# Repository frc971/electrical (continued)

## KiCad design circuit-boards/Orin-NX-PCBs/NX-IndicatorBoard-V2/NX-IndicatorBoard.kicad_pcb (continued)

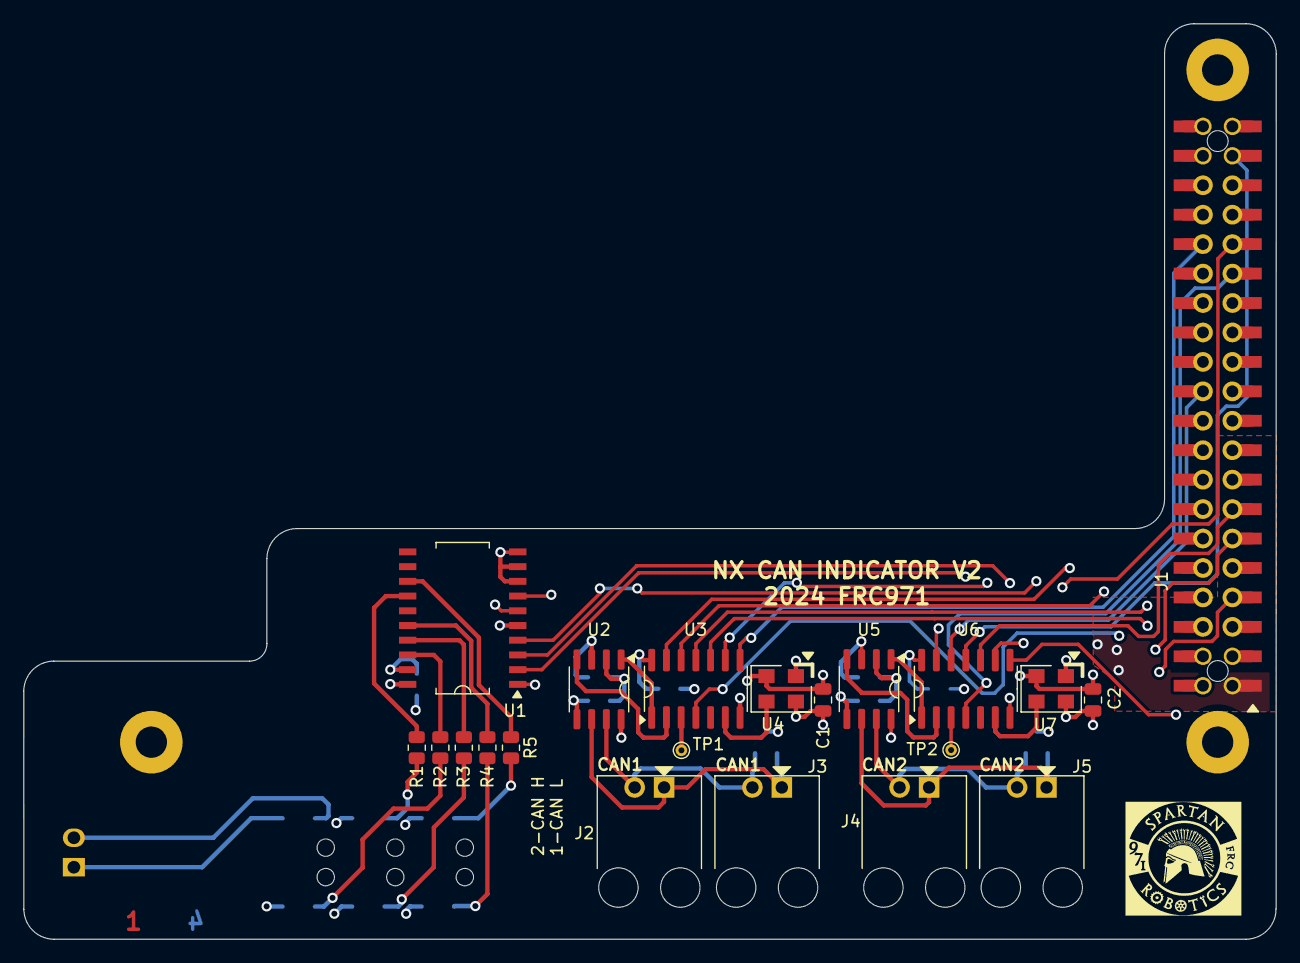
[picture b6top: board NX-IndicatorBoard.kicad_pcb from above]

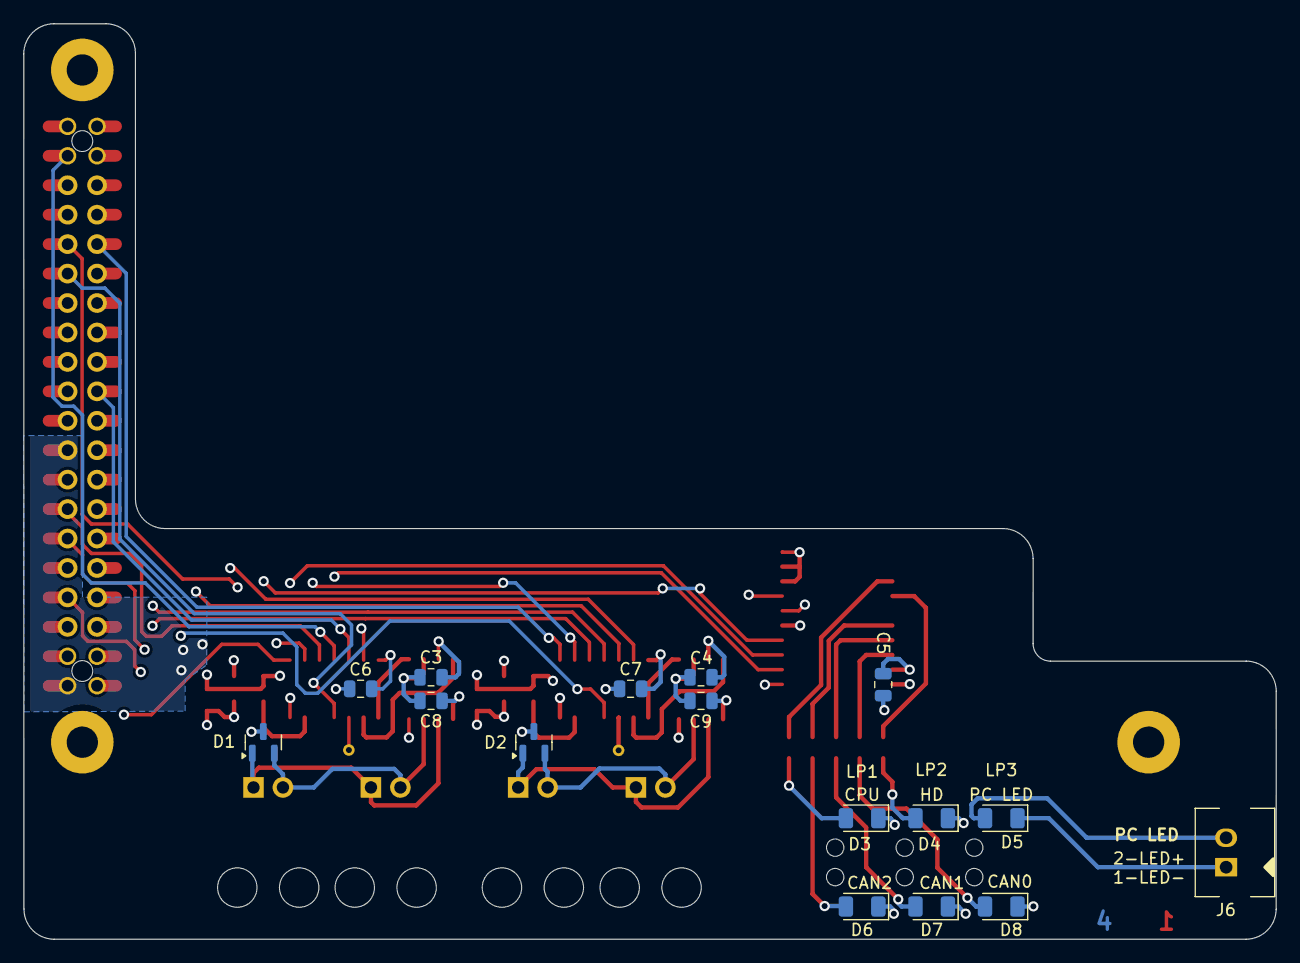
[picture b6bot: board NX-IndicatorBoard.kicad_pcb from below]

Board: 4 copper layers, 108.1 x 79.0 mm, 44 parts (19 on the bottom side), 46 nets.

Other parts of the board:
G1: LOGO; Spartan Logo-FrontSilk

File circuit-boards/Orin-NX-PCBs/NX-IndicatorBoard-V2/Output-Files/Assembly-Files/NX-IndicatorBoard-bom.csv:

"Item","QUANTITY","Reference","Value","MFG","MFG P/N","DIST","DIST P/N"
"1","9","C1-C9","0.1uF-10%-50V-0805","YAGEO","CC0805KRX7R9BB104","Digikey","311-1140-1-ND"
"2","2","D1,D2","PESD1CAN","Nexperia","PESD1CAN,215","Digikey","1727-3817-1-ND"
"3","6","D3-D8","-- mixed values --","Everlight Electronics","QTLP650D4TR","Digikey","1080-1419-1-ND"
"4","1","J1","NX Expansion","Harwin","M20-7812045","Digikey","952-3218-ND"
"5","1","J6","PC LED","Molex","0705430036","Digikey","WM4824-ND"
"6","4","J2-J5","-- mixed values --","Molex","0705550036","Digikey","WM4175-ND"
"7","3","LP1-LP3","Lumex-2x-Light-Pipe","Lumex","LPF-C012303S","Digikey","67-1850-ND"
"8","1","P1","Samtec 40 pin Elevated Socket","Samtec","ESQ-120-34-G-D","Digikey","SAM9319-ND"
"9","5","R1-R5","499R-1%-0805","YAGEO","RC0805FR-07499RL","Digikey","311-499CRCT-ND"
"10","1","U1","74LVC245AD","Nexperia","74LVC245AD,118","Digikey","1727-3104-1-ND"
"11","2","U2,U5","MCP2558FD","Microchip","MCP2558FD-H/SN","Digikey","MCP2558FD-H/SN-ND"
"12","2","U3,U6","MCP2518FDT-H/SL","Microchip","MCP2518FDT-H/SL","Digikey","MCP2518FDT-H/SLCT-ND"
"13","2","U4,U7","40MHz","ECS Inc","ECS-5032MV-400-CN-TR","Digikey","XC3112CT-ND"

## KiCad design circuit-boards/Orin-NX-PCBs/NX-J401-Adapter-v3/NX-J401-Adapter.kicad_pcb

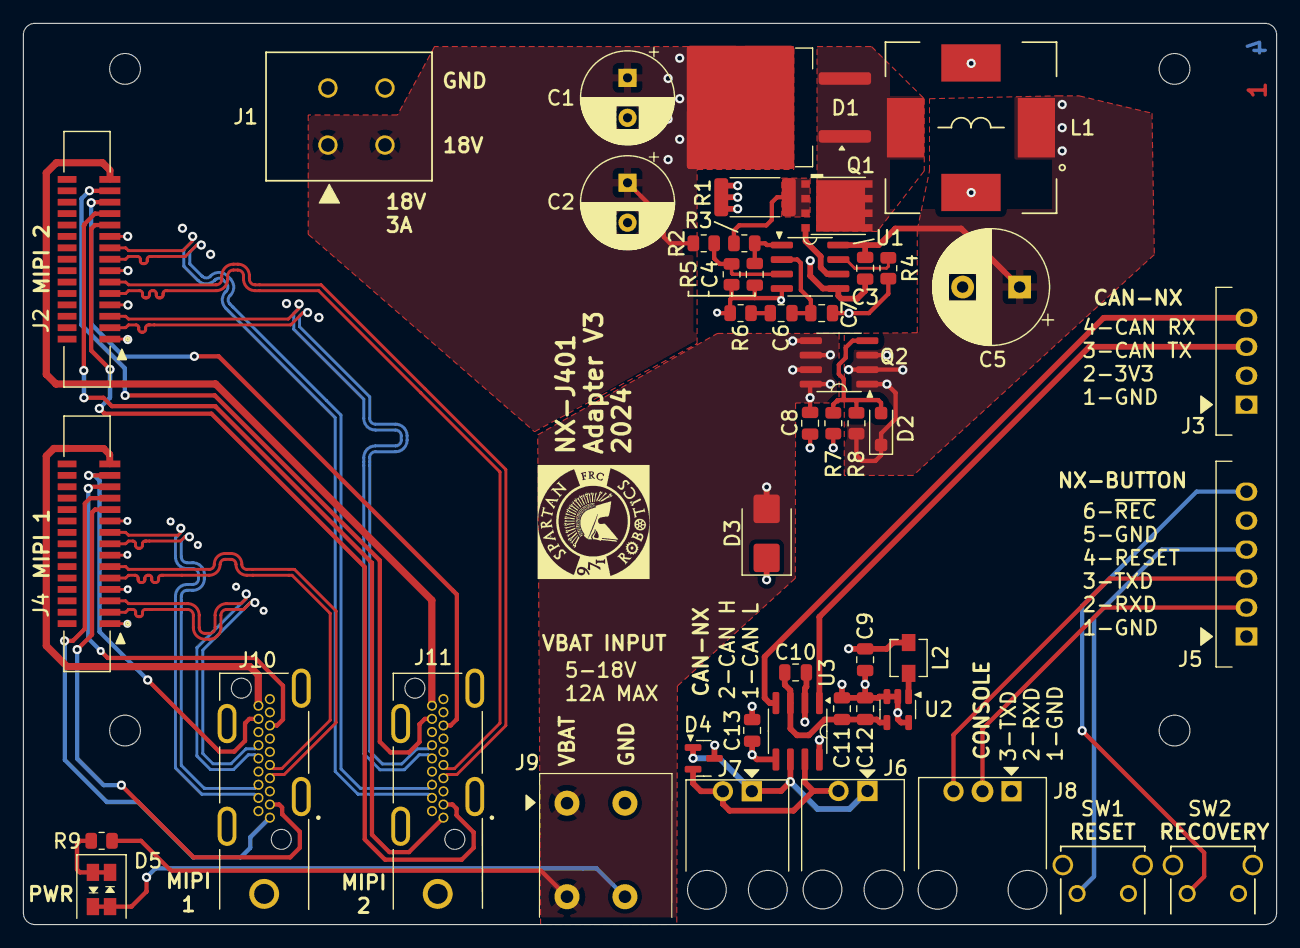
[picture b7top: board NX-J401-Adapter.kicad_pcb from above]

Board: 4 copper layers, 109.9 x 79.0 mm, 51 parts (0 on the bottom side), 51 nets.

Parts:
C1, C2: 82uF 35V; CP_Radial_D8.0mm_P3.50mm
C3, C6, C10, C13: 0.22uF-10%-50V-0805; C_0805_2012Metric
C4: 10pF-5%-50V-0805; C_0805_2012Metric
C5: 330uF 35V; CP_Radial_D10.0mm_P5.00mm
C7: 0.01uF-10%-50V-0805; C_0805_2012Metric
C8, C11, C12: 22uF-20%-25V-0805; C_0805_2012Metric
C9: 10uF-10%-10V-0805; C_0805_2012Metric
D1: STPS20M100SG-TR; TO-263-2
D2: 15V; D_SOD-123F
D3: 15V; D_SMB
D4: PESD1CAN; SOT-23
D5: PWR; LED-Dialight-5913001858F
H1, H2, H3, H4: MountingHole; MountingHole_2.7mm_M2.5
J1: 18V_OUT; CONN_69140872_WRE
J2, J4: MIPI; TE_1-1734248-5
J3: CAN-NX; 70543-0003
J5: NX-BUTTON; 70543-0005
J6, J7: CAN-NX; 70555-0001
J8: CONSOLE; 70555-0002
J9: Power; Wurth-691406510002B
J10, J11: HDMI; SWITCHCRAFT_RAVHD19ETR
L1: 4.7 uH-8m-20%; INDUCTOR_IHLE-5050FH-Vishay
L2: 2.2uH-20%-46mR; L_Vishay_IHLP-1212
Q1: CSD16322Q5; TI-SON5x6
Q2: SI4483ADY-T1-GE3; SOIC-8_3.9x4.9mm_P1.27mm
R1: 4.0m-1%-2512; R_2512_6332Metric
R2: 14.0k-1%-0805; R_0805_2012Metric
R3: 100R-1%-0805; R_0805_2012Metric
R4: 59.0k-1%-0805; R_0805_2012Metric
R5, R6, R7: 1.05k-1%-0805; R_0805_2012Metric
R8: 20.0k-1%-0805; R_0805_2012Metric
R9: 4.99k-1%-0805; R_0805_2012Metric
SW1: RESET; SW_TL1105VF100Q_EWI
SW2: RECOVERY; SW_TL1105VF100Q_EWI
U1: LM3478MA; SOIC-8_3.9x4.9mm_P1.27mm
U2: TPS613222ADBVR; SOT-23-5
U3: MCP2558FD-H/SN; SOIC-8_3.9x4.9mm_P1.27mm

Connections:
/3V3_CAN: C9.1, C13.1, J3.2, L2.1, U3.5 (V_{IO})
/+18V_OUT: C1.1, C2.1, D1.2 (K), J1.1, R2.2
/CAN_H: D4.2 (K1), J6.2, J7.2, U3.7 (CANH)
/CAN_L: D4.1 (K1), J6.1, J7.1, U3.6 (CANL)
/CAN_RX: J3.4, U3.4 (RXD)
/CAN_TX: J3.3, U3.1 (TXD)
/MIPI-HDMI-1/CAM_3V3: J4.15, J10.18 (+5V)
/MIPI-HDMI-1/CAM_CK_N: J4.8, J10.6 (D1-)
/MIPI-HDMI-1/CAM_CK_P: J4.9, J10.4 (D1+)
/MIPI-HDMI-1/CAM_D0_N: J4.2, J10.12 (CK-)
/MIPI-HDMI-1/CAM_D0_P: J4.3, J10.10 (CK+)
/MIPI-HDMI-1/CAM_D1_N: J4.5, J10.9 (D0-)
/MIPI-HDMI-1/CAM_D1_P: J4.6, J10.7 (D0+)
/MIPI-HDMI-1/CAM_MCLK: J4.12, J10.1 (D2+)
/MIPI-HDMI-1/CAM_SCL: J4.13, J10.15 (SCL)
/MIPI-HDMI-1/CAM_SDA: J4.14, J10.16 (SDA)
/MIPI-HDMI-1/GND_MIPI: J4.1, J4.4, J4.7, J4.10, J10.2 (D2S), J10.5 (D1S), J10.8 (D0S), J10.11 (CKS), J10.17 (GND), J10.SH
/MIPI-HDMI-1/PWR_DN_LS: J4.11, J10.3 (D2-)
/MIPI-HDMI-2/CAM_3V3: J2.15, J11.18 (+5V)
/MIPI-HDMI-2/CAM_CK_N: J2.8, J11.6 (D1-)
/MIPI-HDMI-2/CAM_CK_P: J2.9, J11.4 (D1+)
/MIPI-HDMI-2/CAM_D0_N: J2.2, J11.12 (CK-)
/MIPI-HDMI-2/CAM_D0_P: J2.3, J11.10 (CK+)
/MIPI-HDMI-2/CAM_D1_N: J2.5, J11.9 (D0-)
/MIPI-HDMI-2/CAM_D1_P: J2.6, J11.7 (D0+)
/MIPI-HDMI-2/CAM_MCLK: J2.12, J11.1 (D2+)
/MIPI-HDMI-2/CAM_SCL: J2.13, J11.15 (SCL)
/MIPI-HDMI-2/CAM_SDA: J2.14, J11.16 (SDA)
/MIPI-HDMI-2/GND_MIPI: J2.1, J2.4, J2.7, J2.10, J11.2 (D2S), J11.5 (D1S), J11.8 (D0S), J11.11 (CKS), J11.17 (GND), J11.SH
/MIPI-HDMI-2/PWR_DN_LS: J2.11, J11.3 (D2-)
/NX CAN/+5V: C10.1, C11.1, C12.1, U2.4 (VOUT), U3.3 (V_{DD})
/Power Supply/Q_S: Q1.1 (S), Q1.2 (S), Q1.3 (S), R1.2, R3.1
/Power Supply/SW: D1.1 (A), D1.3 (A), L1.2, Q1.5 (D)
/Power Supply/V_IN: C3.1, C5.1, D2.1 (K), L1.1, Q2.1 (S), Q2.2 (S), Q2.3 (S), R8.2, U1.8 (V_{IN})
/RTN: J5.1, J5.5, J8.1, SW1.2, SW2.2
/UART2_RXD: J5.2, J8.2
/UART2_TXD: J5.3, J8.3
/V_BAT: C8.1, D3.2 (A2), J9.1, Q2.5 (D), Q2.6 (D), Q2.7 (D), Q2.8 (D), R9.2
/~REC: J5.6, SW2.1
/~SYS_RESET: J5.4, SW1.1
GND: C1.2, C2.2, C3.2, C4.2, C5.2, C7.2, C8.2, D3.1 (A1), D5.2 (RedA), D5.4 (Green-K), J1.2, J9.2, L1.3, L1.4, R1.1, R4.1, R5.1, R6.1, R7.1, U1.4 (AGND), U1.5 (PGND)
GNDD: C9.2, C10.2, C11.2, C12.2, C13.2, D4.3 (KK), J3.1, U2.2 (GND), U2.3 (NC), U2.5 (NC), U3.2 (V_{SS}), U3.8 (S)
unnamed: C6.2, R6.2
unnamed: D2.2 (A), Q2.4 (G), R7.2, R8.1
unnamed: D5.1 (Red-K), D5.3 (Green-A), R9.1
unnamed: Q1.4 (G), U1.6 (DR)
unnamed: C6.1, C7.1, U1.2 (COMP)
unnamed: R4.2, U1.7 (FA/SD)
unnamed: R2.1, R5.2, U1.3 (FB)
unnamed: C4.1, R3.2, U1.1 (I_{SEN})
unnamed: L2.2, U2.1 (SW)

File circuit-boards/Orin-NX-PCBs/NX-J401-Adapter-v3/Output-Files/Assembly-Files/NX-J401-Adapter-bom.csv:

"Item","QUANTITY","Reference","Value","MFG","MFG P/N","DIST","DIST P/N"
"1","1","C4","10pF-5%-50V-0805","Samsung Electro-Mechanics","CL21C100CBANNNC","Digikey","1276-2561-1-ND"
"2","1","C5","330uF 35V","Rubycon","35PZJ330M10X9","Digikey","1189-35PZJ330M10X9-ND"
"3","1","C7","0.01uF-10%-50V-0805","Samsung Electro-Mechanics","CL21B103KBANNNC","Digikey","1276-1015-1-ND"
"4","1","C9","10uF-10%-10V-0805","Kemet","C0805C106K8PAC7800","Digikey","399-C0805C106K8PAC7800CT-ND"
"5","2","C1,C2","82uF 35V","Panasonic Electronic Components","35SEPF82M","Digikey","P16345-ND"
"6","4","C3,C6,C10,C13","0.22uF-10%-50V-0805","KEMET","C0805C224K5RAC7800","Digikey","399-C0805C224K5RACTUCT-ND"
"7","3","C8,C11,C12","22uF-20%-25V-0805","Samsung Electro-Mechanics","CL21A226MAYNNNE","Digikey","1276-CL21A226MAYNNNECT-ND"
"8","1","D1","STPS20M100SG-TR","STmicroelectronics","STPS20M100SG-TR","Digikey","497-10993-1-ND"
"9","1","D2","15V","Nexperia","BZT52H-C15,115","Digikey","1727-3593-1-ND"
"10","1","D3","15V","Littelfuse","SZ1SMB15CAT3G","Digikey","F11544CT-ND"
"11","1","D4","PESD1CAN","Nexperia","PESD1CAN,215","Digkey","1727-3817-1-ND"
"12","1","D5","PWR","Dialight","5913001858F","Digikey","350-5913001858FCT-ND"
"13","1","J1","18V_OUT","Würth Elektronik","691408720002B","Digikey","732-691408720002B-ND"
"14","1","J3","CAN-NX","Molex","70543-0003","Digikey","WM4802-ND"
"15","1","J5","NX-BUTTON","Molex","0705430040","Digikey","WM4828-ND"
"16","1","J8","CONSOLE","Molex","0705550037","Digikey","WM4176-ND"
"17","1","J9","Power","Wurth","691406510002B","Digikey","732-691406510002B-ND"
"18","2","J10,J11","HDMI","Switchcraft","RAVHD19ETR","Digikey","137-RAVHD19ECT-ND"
"19","2","J2,J4","MIPI","TE Connectivity","1-1734248-5","Digikey","A101418CT-ND"
"20","2","J6,J7","CAN-NX","Molex","0705550036","Digikey","WM4175-ND"
"21","1","L1","4.7 uH-8m-20%","Vishay Dale","IHLE5050FHER4R7M5A ","Mouser","70-IHLE5050FHR4R7M5A "
"22","1","L2","2.2uH-20%-46mR","Vishay","IHLP1212BZER2R2M11","Digikey","541-1322-1-ND"
"23","1","Q1","CSD16322Q5","Texas Instruments","CSD16322Q5","Digikey","296-25112-1-ND"
"24","1","Q2","SI4483ADY-T1-GE3","Vishay","SI4483ADY-T1-GE3","Digikey","SI4483ADY-T1-GE3CT-ND"
"25","1","R1","4.0m-1%-2512","Bourns Inc.","CRE2512-FZ-R004E-3","Digikey","CRE2512-FZ-R004E-3CT-ND"
"26","1","R2","14.0k-1%-0805","Yageo","RC0805FR-0714KL","Digikey","311-14.0KCRCT-ND"
"27","1","R3","100R-1%-0805","Yageo","RC0805FR-07100RL","Digikey","311-100CRCT-ND"
"28","1","R4","59.0k-1%-0805","Yageo","RC0805FR-0759KL","Digikey","311-59.0KCRCT-ND"
"29","1","R9","4.99k-1%-0805","Yageo","RC0805FR-07499RL","Digikey","311-499CRCT-ND"
"30","3","R5-R7","1.05k-1%-0805","Yageo","RC0805FR-071K05L","Digikey","311-1.05KCRCT-ND"
"31","2","SW1,SW2","-- mixed values --","E-Switch","TL1105VF100Q","Digikey","EG2507-ND"
"32","1","U1","LM3478MA","Texas Instruments","LM3478MAX/NOPB","Digikey","296-38111-1-ND"
"33","1","U2","TPS613222ADBVR","Texas Instruments","TPS613222ADBVR","Digikey","296-50503-1-ND"
"34","1","U3","MCP2558FD-H/SN","Microchip","MCP2558FD-H/SN","Digikey","MCP2558FD-H/SN-ND"

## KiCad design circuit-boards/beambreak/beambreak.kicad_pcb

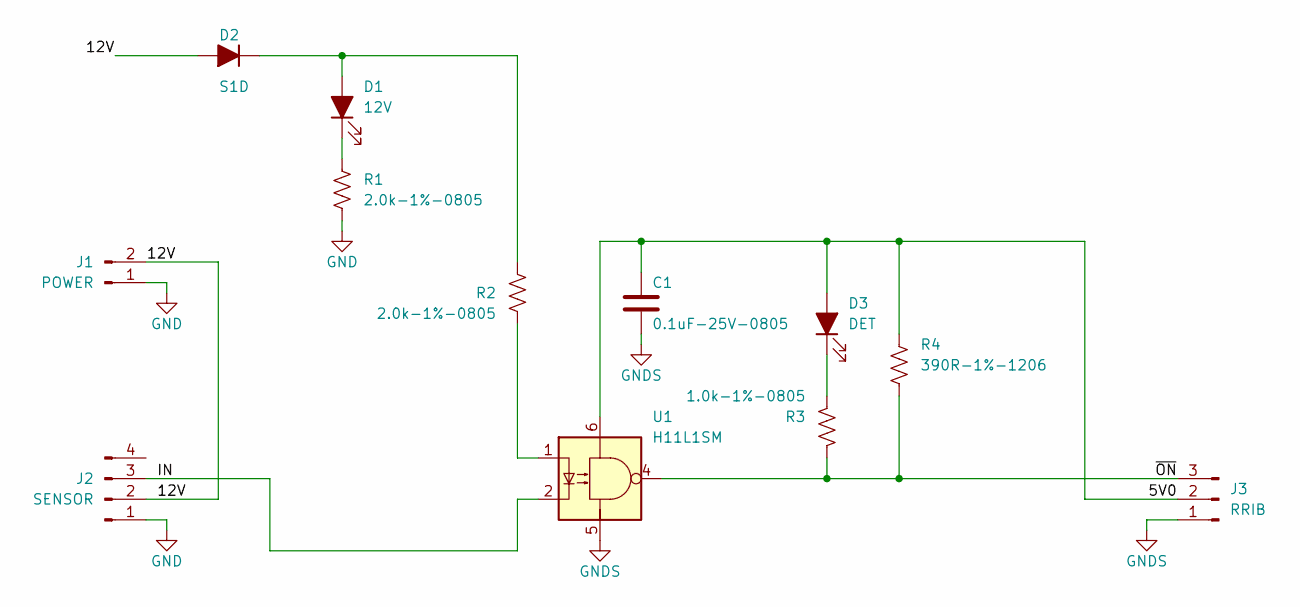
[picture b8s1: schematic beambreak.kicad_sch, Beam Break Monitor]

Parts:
C1: 0.1uF-25V-0805; C_0805_2012Metric
D1: 12V; LED_1206_3216Metric
D2: S1D; D_SMA; MFG P/N S1D-13-F
D3: DET; LED_1206_3216Metric
J1: POWER; Molex-705550001; MFG P/N 705550001
J2: SENSOR; Molex-705550003; MFG P/N 705550003
J3: RRIB; Molex-705550002; MFG P/N 705550002
R1: 2.0k-1%-0805; R_0805_2012Metric; MFG P/N RNCP0805FTD2K00
R2: 2.0k-1%-0805; R_0805_2012Metric
R3: 1.0k-1%-0805; R_0805_2012Metric; MFG P/N RNCP0805FTD1K00
R4: 390R-1%-1206; R_1206_3216Metric; MFG P/N RMCF1206FT390R
U1: H11L1SM; SMDIP-6_W9.53mm; MFG P/N H11L1SM

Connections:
/5V0: C1.1, D3.2 (A), J3.2, R4.2, U1.6
/12V: D2.2 (A), J1.2, J2.2
/IN: J2.3, U1.2
/~ON: J3.3, R3.1, R4.1, U1.4
GND: J1.1, J2.1, R1.1
GNDS: C1.2, J3.1, U1.5
unnamed: D1.1 (K), R1.2
unnamed: D3.1 (K), R3.2
unnamed: D1.2 (A), D2.1 (K), R2.1
unnamed: R2.2, U1.1

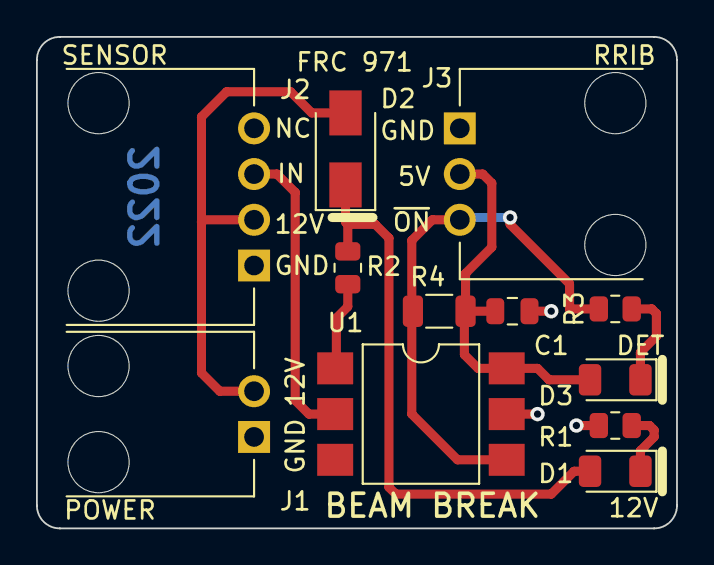
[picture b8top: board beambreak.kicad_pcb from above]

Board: 2 copper layers, 35.6 x 27.3 mm, 12 parts (0 on the bottom side), 10 nets.

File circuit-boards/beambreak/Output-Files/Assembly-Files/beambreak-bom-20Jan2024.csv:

Item, Qty, Reference(s), Value, DIST, DIST P/N, MFG, MFG P/N, 
"1","1","C1","0.1uF-25V-0805","Digikey","478-KGM21NR71E104KTCT-ND","KYOCERA AVX","KGM21NR71E104KT"
"2","2","D1,D3","12V,DET","Digikey","492-1945-1-ND","Bivar Inc.","SM1206NPGC-IL"
"3","1","D2","S1D","Digikey","S1D-FDICT-ND","Diodes Inc","S1D-13-F"
"4","1","J1","POWER","Digikey","WM4164-ND","Molex","705550001"
"5","1","J2","SENSOR","Digikey","WM4166-ND","Molex","705550003"
"6","1","J3","RRIB","Digikey","WM4165-ND","Molex","705550002"
"7","2","R1,R2","2.0k-1%-0805","Digikey","RNCP0805FTD2K00CT-ND","Stackpole Electronics","RNCP0805FTD2K00"
"8","1","R3","1.0k-1%-0805","Digikey","RNCP0805FTD1K00CT-ND","Stackpole Electronics","RNCP0805FTD1K00"
"9","1","R4","390R-1%-1206","Digikey","RMCF1206FT390RCT-ND","Stackpole Electronics","RMCF1206FT390R"
"10","1","U1","H11L1SM","Digikey","H11L1SM-ND","onsemi","H11L1SM"
